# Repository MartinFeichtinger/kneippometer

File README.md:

# kneippometer
This is a project to build a self-sufficient temperatur display for the local kneipp bath.

## power management
The Kneippometer is powered by a compact solar panel, with the generated solar energy stored in a 6V lead-acid battery. To optimize the charging process, we've developed an intelligent charge controller that tracks the Maximum Power Point (MPP) of the solar panel. This allows for charging at the highest possible and permissible power levels at all times.

The display consists of four 7-segment flip-disk indicators, chosen specifically to minimize power consumption. These indicators only require energy during the flipping process, ensuring efficient operation.

## schematic

## pcb layout

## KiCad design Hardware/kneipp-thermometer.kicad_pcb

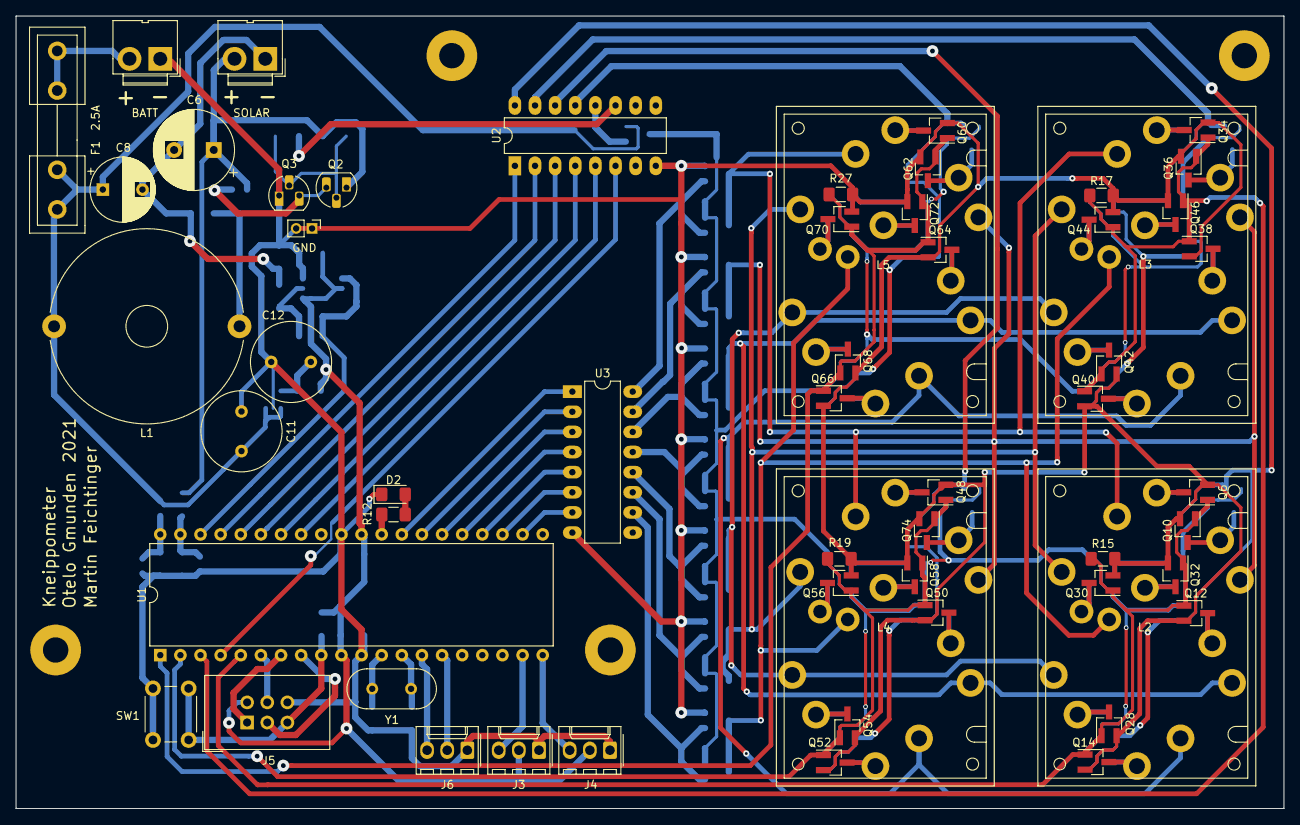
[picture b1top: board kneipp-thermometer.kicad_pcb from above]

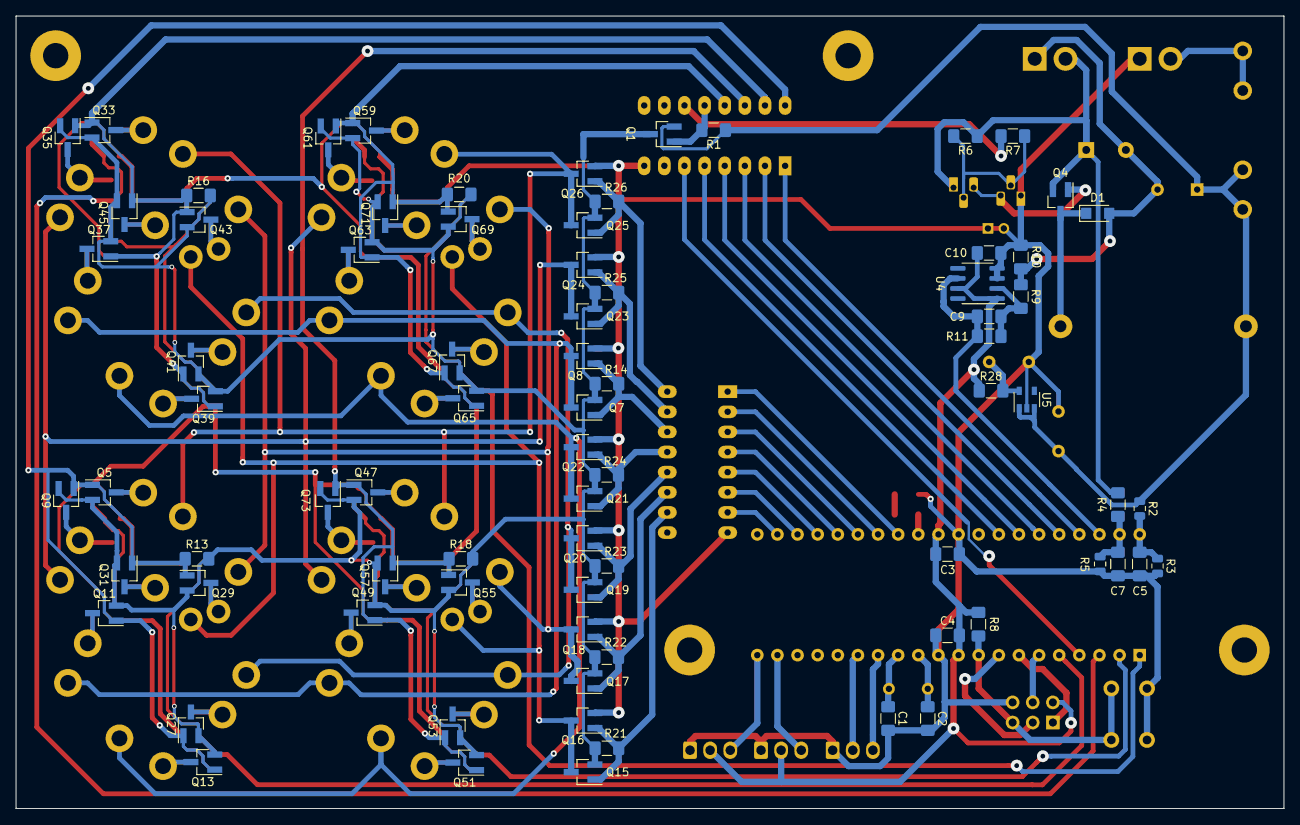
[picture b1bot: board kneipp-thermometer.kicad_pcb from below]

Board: 2 copper layers, 160.0 x 100.0 mm, 136 parts (78 on the bottom side), 92 nets.

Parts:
C1, C2: 22p; C_1206_3216Metric_Pad1.42x1.75mm_HandSolder
C3, C4, C5, C7: 100n; C_1206_3216Metric_Pad1.42x1.75mm_HandSolder
C6: 220µF; CP_Radial_D10.0mm_P5.00mm
C8: 470µF; CP_Radial_D8.0mm_P5.00mm
C9, C10: 100nF; C_1206_3216Metric_Pad1.42x1.75mm_HandSolder
C11: 22µF; C_Radial_D10.0mm_H12.5mm_P5.00mm
C12: 1µF; C_Radial_D10.0mm_H12.5mm_P5.00mm
D1: DP2X414; D_SMF
D2: LED; LED_1206_3216Metric_Pad1.42x1.75mm_HandSolder
F1: 2.5A; Fuseholder5x20_horiz_open_inline_Type-I
GND: TestPoint GND; PinHeader_1x02_P2.00mm_Vertical
J1: BATT; JWT_A3963_1x02_P3.96mm_Vertical
J2: SOLAR; JWT_A3963_1x02_P3.96mm_Vertical
J3: TempAir; Molex_KK-254_AE-6410-03A_1x03_P2.54mm_Vertical
J4: TempWater; Molex_KK-254_AE-6410-03A_1x03_P2.54mm_Vertical
J5: ISP; IDC-Header_2x03_P2.54mm_Vertical
J6: Rx/Tx; Molex_KK-254_AE-6410-03A_1x03_P2.54mm_Vertical
L1: 2.2mH; L_Radial_D24.4mm_P23.40mm_muRATA_1400series
L2, L3, L4, L5: 7-Segment-Anzeige
Q1, Q4, Q5, Q7, Q9, Q11, Q13, Q15, Q17, Q19, Q21, Q23, Q25, Q27, Q29, Q31, Q33, Q35, Q37, Q39, Q41, Q43, Q45, Q47, Q49, Q51, Q53, Q55, Q57, Q59, Q61, Q63, Q65, Q67, Q69, Q71, Q73: DMP 3098L7 DII; SOT-23_Handsoldering
Q2: BC547; TO-92_HandSolder
Q3: BC327; TO-92_HandSolder
Q6, Q8, Q10, Q12, Q14, Q16, Q18, Q20, Q22, Q24, Q26, Q28, Q30, Q32, Q34, Q36, Q38, Q40, Q42, Q44, Q46, Q48, Q50, Q52, Q54, Q56, Q58, Q60, Q62, Q64, Q66, Q68, Q70, Q72, Q74: AO3418; SOT-23_Handsoldering
R1, R14, R21, R22, R23, R24, R25, R26: 2.2k; R_1206_3216Metric_Pad1.42x1.75mm_HandSolder
R2, R3, R5: 47k; R_0805_2012Metric
R4: 180k; R_1206_3216Metric_Pad1.42x1.75mm_HandSolder
R6, R7: 5.6k; R_1206_3216Metric_Pad1.42x1.75mm_HandSolder
R8, R11: 10k; R_1206_3216Metric_Pad1.42x1.75mm_HandSolder
R9: 100; R_1206_3216Metric_Pad1.42x1.75mm_HandSolder
R10: 0.1; R_1206_3216Metric_Pad1.42x1.75mm_HandSolder
R12: 1k; R_1206_3216Metric_Pad1.42x1.75mm_HandSolder
R13, R15, R16, R17, R18, R19, R20, R27: 2k2; R_1206_3216Metric_Pad1.42x1.75mm_HandSolder
R28: 0R; R_1206_3216Metric_Pad1.42x1.75mm_HandSolder
SW1: SW_Push; SW_PUSH_6mm
U1: ATmega16A-PU; DIP-40_W15.24mm
U2, U3: ULN2003A; DIP-16_W7.62mm_LongPads
U4: MAX4238ASA; SOIC-8_3.9x4.9mm_P1.27mm
U5: TC1017-xCT; SOT-23-5
Y1: 4MHz; Crystal_HC18-U_Vertical

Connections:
+5V: C3.1, C4.2, C10.2, J3.2, J4.2, J5.2, R8.1, R28.1, U1.10, U1.30, U4.1, U4.7
+6V: Q1.3, Q5.2, Q7.2, Q9.2, Q11.2, Q13.2, Q15.2, Q17.2, Q19.2, Q21.2, Q23.2, Q25.2, Q27.2, Q29.2, Q31.2, Q33.2, Q35.2, Q37.2, Q39.2, Q41.2, Q43.2, Q45.2, Q47.2, Q49.2, Q51.2, Q53.2, Q55.2, Q57.2, Q59.2, Q61.2, Q63.2, Q65.2, Q67.2, Q69.2, Q71.2, Q73.2, R13.2, R14.1, R16.2, R18.2, R20.2, R21.1, R22.1, R23.1, R24.1, R25.1, R26.1
+BATT: C8.1, C11.2, F1.2, L1.2, Q1.2, R1.1, R2.1, U5.1, U5.3
/B1/In: Q25.1, Q26.1, R26.2, U3.16
/B1/Output: L2.1, L3.1, L4.1, L5.1, Q25.3, Q26.3
/B2/In: Q23.1, Q24.1, R25.2, U3.15
/B2/Output: L2.3, L3.3, L4.3, L5.3, Q23.3, Q24.3
/B3/In: Q7.1, Q8.1, R14.2, U3.14
/B3/Output: L2.5, L3.5, L4.5, L5.5, Q7.3, Q8.3
/B4/In: Q21.1, Q22.1, R24.2, U3.13
/B4/Output: L2.7, L3.7, L4.7, L5.7, Q21.3, Q22.3
/B5/In: Q19.1, Q20.1, R23.2, U3.12
/B5/Output: L2.9, L3.9, L4.9, L5.9, Q19.3, Q20.3
/B6/In: Q17.1, Q18.1, R22.2, U3.11
/B6/Output: L2.11, L3.11, L4.11, L5.11, Q17.3, Q18.3
/B7/In: Q15.1, Q16.1, R21.2, U3.10
/B7/Output: L2.13, L3.13, L4.13, L5.13, Q15.3, Q16.3
/H1/O: L2.2, Q5.3, Q6.3
/H2/O: L2.4, Q9.3, Q10.3
/H3/O: L2.6, Q11.3, Q12.3
/H4/O: L2.8, Q13.3, Q14.3
/H5/O: L2.10, Q27.3, Q28.3
/H6/O: L2.12, Q29.3, Q30.3
/H7/O: L2.14, Q31.3, Q32.3
/H8/O: L3.2, Q33.3, Q34.3
/H9/O: L3.4, Q35.3, Q36.3
/H10/O: L3.6, Q37.3, Q38.3
/H11/O: L3.8, Q39.3, Q40.3
/H12/O: L3.10, Q41.3, Q42.3
/H13/O: L3.12, Q43.3, Q44.3
/H14/O: L3.14, Q45.3, Q46.3
/H15/O: L4.2, Q47.3, Q48.3
/H16/O: L4.4, Q73.3, Q74.3
/H17/O: L4.6, Q49.3, Q50.3
/H18/O: L4.8, Q51.3, Q52.3
/H19/O: L4.10, Q53.3, Q54.3
/H20/O: L4.12, Q55.3, Q56.3
/H21/O: L4.14, Q57.3, Q58.3
/H22/O: L5.2, Q59.3, Q60.3
/H23/O: L5.4, Q61.3, Q62.3
/H24/O: L5.6, Q63.3, Q64.3
/H25/O: L5.8, Q65.3, Q66.3
/H26/O: L5.10, Q67.3, Q68.3
/H27/O: L5.12, Q69.3, Q70.3
/H28/O: L5.14, Q71.3, Q72.3
/HIGH8: Q5.1, Q9.1, Q11.1, Q13.1, Q27.1, Q29.1, Q31.1, R13.1, U2.16
/HIGH9: Q33.1, Q35.1, Q37.1, Q39.1, Q41.1, Q43.1, Q45.1, R16.1, U2.15
/HIGH10: Q47.1, Q49.1, Q51.1, Q53.1, Q55.1, Q57.1, Q73.1, R18.1, U2.14
/HIGH11: Q59.1, Q61.1, Q63.1, Q65.1, Q67.1, Q69.1, Q71.1, R20.1, U2.13
/LOW8: Q6.1, Q10.1, Q12.1, Q14.1, Q28.1, Q30.1, Q32.1, R15.2, U1.5
/LOW9: Q34.1, Q36.1, Q38.1, Q40.1, Q42.1, Q44.1, Q46.1, R17.2, U1.3
/LOW10: Q48.1, Q50.1, Q52.1, Q54.1, Q56.1, Q58.1, Q74.1, R19.2, U1.2
/LOW11: Q60.1, Q62.1, Q64.1, Q66.1, Q68.1, Q70.1, Q72.1, R27.2, U1.1
/MISO: J5.1, U1.7
/MOSI: J5.4, U1.6
/PA3: U1.37, U2.1
/PA4: U1.36, U2.2
/PA5: U1.35, U2.3
/PA6: U1.34, U2.4
/PA7: U1.33, U2.5
/PC0: U1.22, U3.7
/PC1: U1.23, U3.6
/PC2: U1.24, U3.5
/PC3: U1.25, U3.4
/PC4: U1.26, U3.3
/PC5: U1.27, U3.2
/PC6: U1.28, U3.1
/PWM: U1.4, U2.6
/RESET: J5.5, R8.2, SW1.2, U1.9
/SCK: J5.3, U1.8
/TempAir: J3.3, U1.19
/TempWater: J4.3, U1.20
/VShunt: C9.1, R11.1, U1.38, U4.6
GND: C1.2, C2.2, C3.2, C4.1, C5.1, C7.1, C10.1, C11.1, C12.1, D2.1, GND.1, GND.2, J1.1, J3.1, J4.1, J5.6, J6.1, Q3.1, Q6.2, Q8.2, Q10.2, Q12.2, Q14.2, Q16.2, Q18.2, Q20.2, Q22.2, Q24.2, Q26.2, Q28.2, Q30.2, Q32.2, Q34.2, Q36.2, Q38.2, Q40.2, Q42.2, Q44.2, Q46.2, Q48.2, Q50.2, Q52.2, Q54.2, Q56.2, Q58.2, Q60.2, Q62.2, Q64.2, Q66.2, Q68.2, Q70.2, Q72.2, Q74.2, R3.2, R5.2, R10.1, R15.1, R17.1, R19.1, R27.1, SW1.1, U1.11, U1.31, U2.8, U3.8, U4.3, U4.4, U5.2
unnamed: C1.1, U1.13, Y1.2
unnamed: C2.1, U1.12, Y1.1
unnamed: C5.2, R2.2, R3.1, U1.40
unnamed: C6.2, C8.2, D1.2, J2.1, R9.2, R10.2
unnamed: C7.2, R4.2, R5.1, U1.39
unnamed: C9.2, R9.1, R11.2, U4.2
unnamed: C12.2, R28.2, U5.5
unnamed: D1.1, L1.1, Q4.3
unnamed: D2.2, R12.1
unnamed: F1.1, J1.2
unnamed: J6.2, U1.15
unnamed: J6.3, U1.14
unnamed: Q1.1, R1.2, U2.12
unnamed: Q2.2, Q3.2, R6.2, R7.1
unnamed: Q2.3, Q3.3, Q4.1
unnamed: R7.2, U2.11
unnamed: R12.2, U1.29
VCC: C6.1, J2.2, Q2.1, Q4.2, R4.1, R6.1

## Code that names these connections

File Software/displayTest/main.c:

#include <avr/io.h>
#include <math.h>
#include <stdbool.h>
#include <string.h>
#include <stdio.h>

#include "display.h"


#define NDIGITS 4

// digit Pins
#define HIGH0	(1<<PA6)
#define HIGH1	(1<<PA4)
#define HIGH2	(1<<PA5)
#define HIGH3	(1<<PA3)
#define LOW0	(1<<PB0)
#define LOW1	(1<<PB2)
#define LOW2	(1<<PB1)
#define LOW3	(1<<PB4)

// segment Pins
#define SEG0	(1<<PC6)
#define SEG1	(1<<PC5)
#define SEG2	(1<<PC4)
#define SEG3	(1<<PC3)
#define SEG4	(1<<PC2)
#define SEG5	(1<<PC1)
#define SEG6	(1<<PC0)

#define LED_ON	PORTC |= (1<<PC7)
#define LED_OFF	PORTC &= (~(1<<PC7))

#define BAUD	25	// 9600 baud

void wait(uint32_t time_ms);		// wait funktion
void send(char string[]);


// ************ main function ****************
int main(void)
{
	// initiate serial communication
	UBRRH=(unsigned char) (BAUD>>8);	// baudrate
	UBRRL=(unsigned char) BAUD;
	UCSRB=(1<<RXEN)|(1<<TXEN);			// enable receiver and transmitter
	UCSRC=(1<<URSEL)|(3<<UCSZ0);		// 8 Bit
	
	DDRA |= HIGH0|HIGH1|HIGH2|HIGH3|(1<<PA7);
	DDRB |= LOW0|LOW1|LOW2|LOW3;
	DDRC |= 0xff;
	DDRD |= 0x00;
	
	PORTA = 0x00;
	PORTB = 0x00;
	PORTC = 0x00;
	PORTD = 0x00;
	PORTC &= (~(1<<PC7));	// LED
	
	int tempWater=88;
	int tempAir=88;

	DISPLAY_clearDisplay();
	while(true)
	{
		send("stayAlive\n");
		//DISPLAY_printTemp(0, 0);	// tempAir, tempWater
		send("clear display...\n");
		LED_ON;
		DISPLAY_clearDisplay();
		wait(2000);
		
		send("open display...\n");
		LED_OFF;
		DISPLAY_printTemp(tempAir, tempWater);
		wait(2000);
	}
	
	return 0;
}


void wait(uint32_t time_ms)	  			// wait function
{
	time_ms*=2;
	TCCR0=0x02;		// 8 prescaler
	while(time_ms>0)
	{
		while(!(TIFR & 0x01));
		TIFR |= 0x01; //clear TOV0 
		time_ms--;
	}
}


// function to send a string over the serial port.
// WARNING: this function blocks until the whole string is sent.
void send(char string[])
{
	int i=0;							// point to first character
	while(string[i]!='\0')				// do until end of string ('\0') is reached
	{
		while(!(UCSRA & (1<<UDRE)));	// wait until serial port is free for next character
		UDR=string[i];					// send character
		i++;							// next character
	}
}

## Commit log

2024-08-17 Finished projec. There will be just some small bug fixes
2024-09-28 Fixed bug. The kneippometer is now able to recover itself when the batterie voltage gets to low
